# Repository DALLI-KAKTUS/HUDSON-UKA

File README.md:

# HUDSON-UKA
an rc car project for learning electronics, mechanics, and programming. made by izmir katip çelebi university İKÇÜTEKNO.

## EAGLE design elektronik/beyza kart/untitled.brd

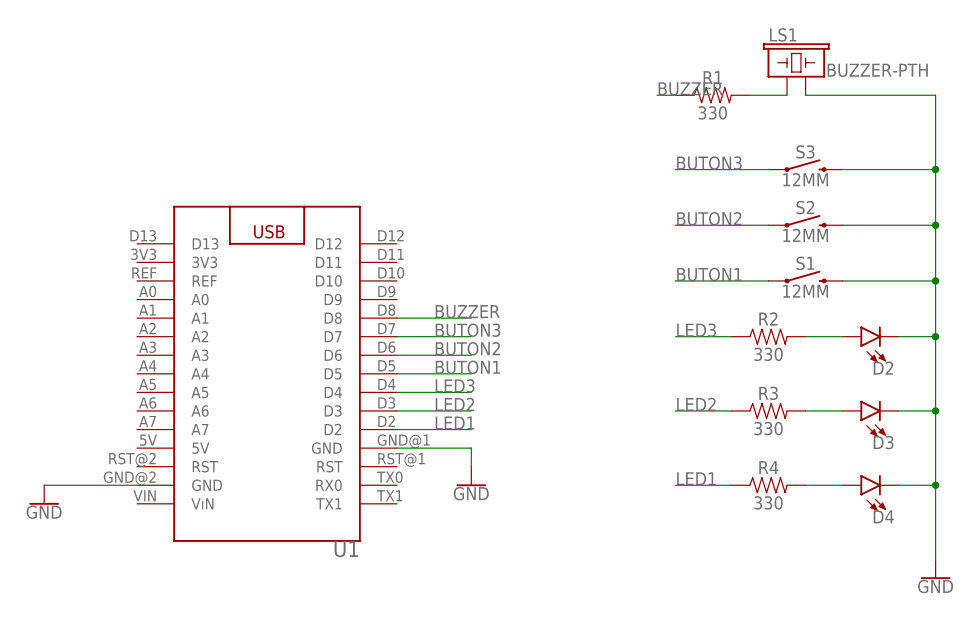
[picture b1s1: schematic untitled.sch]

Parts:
D2, D3, D4: LED-3MM-NO_SILK; LED_3MM-NS
LS1: BUZZER-PTH; BUZZER-12MM
R1, R2, R3, R4: 330; AXIAL-0.3
S1, S2, S3: 12MM; TACTILE_SWITCH_PTH_12MM
U1: ARDUINO_NANO

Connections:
BUTON1: S1.1, U1.D5
BUTON2: S2.1, U1.D6
BUTON3: S3.1, U1.D7
BUZZER: R1.P$1 (1), U1.D8
GND: D2.K (C), D3.K (C), D4.K (C), LS1.- (2), S1.3 (2), S2.3 (2), S3.3 (2), U1.GND@1 (GND), U1.GND@2 (GND)
LED1: R4.P$1 (1), U1.D2
LED2: R3.P$1 (1), U1.D3
LED3: R2.P$1 (1), U1.D4
unnamed: LS1.+ (1), R1.P$2 (2)
unnamed: D2.A, R2.P$2 (2)
unnamed: D3.A, R3.P$2 (2)
unnamed: D4.A, R4.P$2 (2)

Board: 2 copper layers, 12 parts (0 on the bottom side), 12 nets, no tracks yet.

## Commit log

2023-02-03 m
    m
2023-02-03 Create m
2023-02-03 Create kumanda
2023-02-03 Create Direksiyon Sistemi Kaba Taslak
2023-02-03 Kumanda devresi
2023-02-04 redüktör
2023-02-25 Create Süspansiyon+Direksiyon Sistemi
2023-03-01 toplantı sırasında
    şase dosyasını klasörledim
    deneme dostyası oluşturdum
2023-03-01 beyza kart eklendi
2023-03-05 iki dosya silindi gereksiz
2023-03-08 Create şaft
2023-03-08 şaft
2023-03-08 Revert "Add files via upload"
    This reverts commit 71b3ca1d67eb1077498db1e4198db27c9279f16c.
2023-03-08 ESC_Model
2023-03-22 Create fin
2023-03-22 final/
2023-03-22 Add files via upload
    AÇARKEN HEPĞSİNİ İNDERMENİZ ÖNEMLE RİCA OLUNUR
2023-03-24 Create süspansiyon (olup olmadığı denemek için açıldı)
2023-03-25 bldc motor

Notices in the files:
parts and their libraries:
SparkFun-LED: Licensing: Creative Commons ShareAlike 4.0 International - https://creativecommons.org/licenses/by-sa/4.0
